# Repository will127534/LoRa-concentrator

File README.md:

# LoRa-concentrator

A Real opensource LoRa Gateway using SX1301/SX1308 and SX1255/SX1257
For RRI and RPI Zero

**Version 3**
---

Version 3 is designed for Raspberry Pi, same setup like Version 2, but I added LNA/PA and RF switch, and move to 4-layer board design
PA(RFPA0133) and RF switch(RFSW1012) is same as Microchip's LoRa gateway, but I changed LNA to SKY67150-396LF which have a much better Noise Figure(0.28dB).
Also note that I also used a wide bandwidth ceramic balun(800-1000Mhz) instead of discrete balun.

868Mhz and 915Mhz is mostly the same, just need to change four filter, both part number are in PCB files and BOM file. 

For power supply, 1.8V DC-DC step down has changed to TPS62061, but it is pin-to-pin replaceable with ETA3410. For 3.3V RF power, there is two option,
one is TPS7A470, which is a Ti's high-end LDO with 4 µVRMS noise, and 55dB PSRR, the other one is LP5912-3.3, which is cheaper but still gets 12 µVRMS noise and 75dB PSRR.

GPS module is still Max-7Q, which provide PPS to SX1301/8 and Raspberry Pi(GPIO05),
and provide NEMA through Raspberry Pi's UART port. There is a jumper for shuting down GPS module if you want to stack other board.

Lastly, it support PoE header on Raspberry Pi 3B+, so you can stack PoE hat on top of the board.(Just make it clear that the board doesn't have PoE on board, but just the pin header to support other PoE hat).

And is currently sold on Tindle!
https://www.tindie.com/products/will123321/sx1308-raspberry-pi-zero-lora-gateway-board/
https://www.tindie.com/products/will123321/sx1308-raspberry-pi-lora-gateway-board/

Update: 2021/08/22: The board has sold out!

**Version 2**
---
Version 2 is designed for Raspberry Pi and another board for Pi Zero

for Raspberry Pi, there is two SX125X, but for Pi Zero I strip down Radio_A for better layout.
Both of them have a Max-7Q GPS module, which provide PPS to SX1301 and Raspberry Pi(GPIO05),
and provide NEMA through Raspberry Pi's UART port. There's also a jumper for shuting down GPS module if you want to stack other board.

At the RF frontend, the main difference is that I didn't combine RX/TX using a RF switch,
and there is no on-board PA/LNA, but I did put a SAW filter. The reason not to is that I can use external LNA which is right under the antenna, there is a bias inductor right after RX port, which is connected to Raspberry Pi's 5V power rail.  

The current RPI version is designed for SX1257, but it is easy to migrate to SX1255, just put SX1255 on SX1257 and change RF passive components according to SX1255 datasheet.

I've tested both SX1255 & SX1257, and also two SX1301 connected to Raspberry Pi at the same time (there is a jumper for CE0/CE1).

last but not least, I've launch some High Altitude Balloon and using it as my multi-channel receiver. Which reach about 100Km by BW 125Khz CR 4/5 SF 7 @ 432Mhz with 16dBm power + MAX2640 LNA.

**Version 1**
---
note that I haven't get it working yet, stuck in PLL lock  
but SPI test seems to be OK.

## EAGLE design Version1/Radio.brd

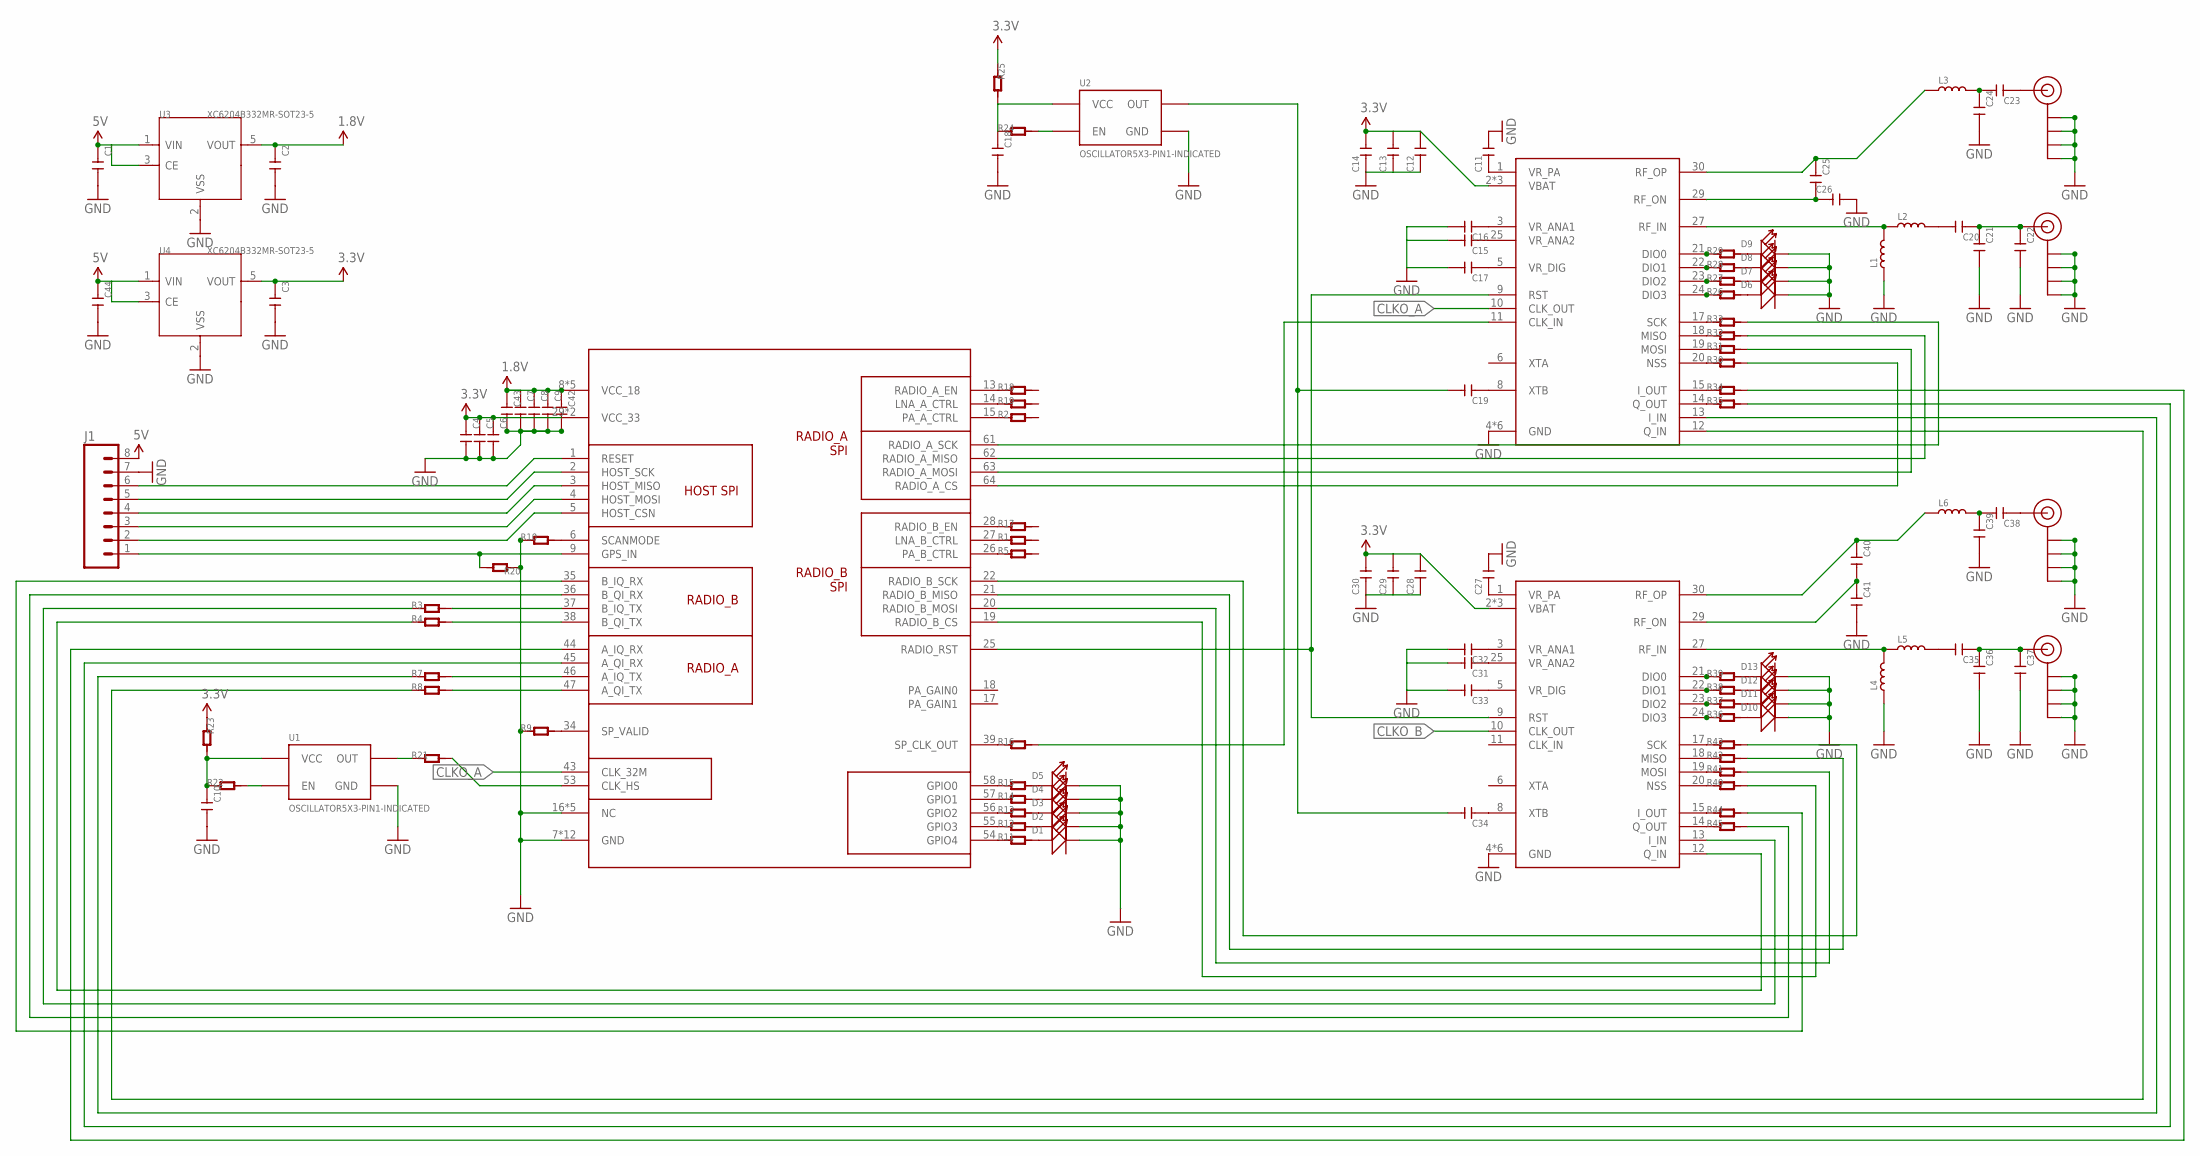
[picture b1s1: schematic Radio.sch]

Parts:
C1, C3: CAP-0603; C0603
C2, C4, C6, C7, C8, C9, C10, C11, C12, C13, C14, C15, C16, C17, C18, C19, C20, C21, C22, C23, C24, C25, C26, C27, C28, C29, C30, C31, C32, C33, C34, C35, C36, C37, C38, C39, C40, C41, C42, C43, C44: CAP-0402; C0402
C5: CAP-0805; C0805
D1, D2, D3, D4, D5, D6, D7, D8, D9, D10, D11, D12, D13: LED-0402
J1: M08LOCK; 1X08_LOCK
J$1, J$2, J$3, J$4: SMA_EDGE; SMA-EDGE
L1, L2, L3, L4, L5, L6: INDUCTOR/FERRITE-BEAD-0402; L0402
R1, R2, R3, R4, R5, R7, R8, R9, R10, R11, R12, R13, R14, R15, R16, R17, R18, R19, R20, R21, R22, R23, R24, R25, R26, R27, R28, R29, R30, R31, R32, R33, R34, R35, R36, R37, R38, R39, R40, R41, R42, R43, R44, R45: R-0402; R0402
U1, U2: OSCILLATOR5X3-PIN1-INDICATED; CRYSTAL-OSC-SMD-5X3
U3, U4: XC6204B332MR-SOT23-5; SOT-23-5
U$1: SX1301; QFN64G-0.5-9X9MM
U$2, U$3: SX1255; QFN32G-0.5-5X5MM

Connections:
1.8V: C2.1, C7.1, C8.1, C9.1, C42.1, C43.1, U3.5 (VOUT), U$1.8 (VCC_18), U$1.12 (VCC_18), U$1.23 (VCC_18), U$1.42 (VCC_18), U$1.60 (VCC_18)
3.3V: C3.1, C4.1, C5.1, C6.1, C12.2, C13.2, C14.2, C28.2, C29.2, C30.2, R23.1, R25.1, U4.5 (VOUT), U$1.29 (VCC_33), U$1.52 (VCC_33), U$2.2 (VBAT), U$2.16 (VBAT), U$2.32 (VBAT), U$3.2 (VBAT), U$3.16 (VBAT), U$3.32 (VBAT)
5V: C1.1, C44.1, J1.8, U3.1 (VIN), U3.3 (CE), U4.1 (VIN), U4.3 (CE)
CLKO_A: U$1.43 (CLK_32M), U$2.10 (CLK_OUT)
CLKO_B: U$3.10 (CLK_OUT)
CS: J1.2, U$1.5 (HOST_CSN)
GND: C1.2, C2.2, C3.2, C4.2, C5.2, C6.2, C7.2, C8.2, C9.2, C10.2, C11.2, C12.1, C13.1, C14.1, C15.2, C16.2, C17.2, C18.2, C21.2, C22.2, C24.2, C26.2, C27.2, C28.1, C29.1, C30.1, C31.2, C32.2, C33.2, C36.2, C37.2, C39.2, C41.2, C42.2, C43.2, C44.2, D1.-, D2.-, D3.-, D4.-, D5.-, D6.-, D7.-, D8.-, D9.-, D10.-, D11.-, D12.-, D13.-, J1.7, J$1.GND@0 (GND), J$1.GND@1 (GND), J$1.GND@2 (GND), J$1.GND@3 (GND), J$2.GND@0 (GND), J$2.GND@1 (GND), J$2.GND@2 (GND), J$2.GND@3 (GND), J$3.GND@0 (GND), J$3.GND@1 (GND), J$3.GND@2 (GND), J$3.GND@3 (GND), J$4.GND@0 (GND), J$4.GND@1 (GND), J$4.GND@2 (GND), J$4.GND@3 (GND), L1.1, L4.1, R9.1, R10.1, R20.1, U1.2 (GND), U2.2 (GND), U3.2 (VSS), U4.2 (VSS), U$1.7 (GND), U$1.10 (GND), U$1.11 (GND), U$1.16 (NC), U$1.24 (GND), U$1.30 (GND), U$1.31 (GND), U$1.32 (NC), U$1.33 (NC), U$1.40 (GND), U$1.41 (GND), U$1.48 (NC), U$1.49 (NC), U$1.50 (GND), U$1.51 (GND), U$1.59 (GND), U$1.65 (GND), U$2.4 (GND), U$2.7 (GND), U$2.26 (GND), U$2.28 (GND), U$2.31 (GND), U$2.33 (GND), U$3.4 (GND), U$3.7 (GND), U$3.26 (GND), U$3.28 (GND), U$3.31 (GND), U$3.33 (GND)
MISO: J1.4, U$1.3 (HOST_MISO)
MOSI: J1.3, U$1.4 (HOST_MOSI)
unnamed: R30.1, U$2.20 (NSS)
unnamed: R45.2, U$1.36 (B_QI_RX)
unnamed: R3.2, U$1.37 (B_IQ_TX)
unnamed: R4.2, U$1.38 (B_QI_TX)
unnamed: R34.2, U$1.44 (A_IQ_RX)
unnamed: R7.2, U$1.46 (A_IQ_TX)
unnamed: R8.2, U$1.47 (A_QI_TX)
unnamed: R35.2, U$1.45 (A_QI_RX)
unnamed: R9.2, U$1.34 (SP_VALID)
unnamed: R10.2, U$1.6 (SCANMODE)
unnamed: R1.1, U$1.27 (LNA_B_CTRL)
unnamed: R11.1, U$1.54 (GPIO4)
unnamed: R12.1, U$1.55 (GPIO3)
unnamed: R13.1, U$1.56 (GPIO2)
unnamed: R14.1, U$1.57 (GPIO1)
unnamed: R15.1, U$1.58 (GPIO0)
unnamed: D1.+, R11.2
unnamed: D2.+, R12.2
unnamed: D4.+, R14.2
unnamed: D5.+, R15.2
unnamed: D3.+, R13.2
unnamed: R16.1, U$1.39 (SP_CLK_OUT)
unnamed: R17.1, U$1.28 (RADIO_B_EN)
unnamed: R18.1, U$1.13 (RADIO_A_EN)
unnamed: R2.1, U$1.15 (PA_A_CTRL)
unnamed: R19.1, U$1.14 (LNA_A_CTRL)
unnamed: R5.1, U$1.26 (PA_B_CTRL)
unnamed: C19.1, U$2.8 (XTB)
unnamed: R21.2, U$1.53 (CLK_HS)
unnamed: R21.1, U1.3 (OUT)
unnamed: R22.2, U1.1 (EN)
unnamed: C10.1, R22.1, R23.2, U1.4 (VCC)
unnamed: R24.2, U2.1 (EN)
unnamed: C11.1, U$2.1 (VR_PA)
unnamed: C18.1, R24.1, R25.2, U2.4 (VCC)
unnamed: C19.2, C34.2, U2.3 (OUT)
unnamed: C15.1, U$2.25 (VR_ANA2)
unnamed: C16.1, U$2.3 (VR_ANA1)
unnamed: C17.1, U$2.5 (VR_DIG)
unnamed: R26.1, U$2.24 (DIO3)
unnamed: R27.1, U$2.23 (DIO2)
unnamed: R28.1, U$2.22 (DIO1)
unnamed: R29.1, U$2.21 (DIO0)
unnamed: D6.+, R26.2
unnamed: D8.+, R28.2
unnamed: D9.+, R29.2
unnamed: D7.+, R27.2
unnamed: L1.2, L2.1, U$2.27 (RF_IN)
unnamed: C20.2, L2.2
unnamed: C20.1, C21.1, C22.1, J$1.SIG (SIGNAL)
unnamed: C23.2, C24.1, L3.2
unnamed: C25.1, L3.1, U$2.30 (RF_OP)
unnamed: C25.2, C26.1, U$2.29 (RF_ON)
unnamed: C23.1, J$2.SIG (SIGNAL)
unnamed: R34.1, U$2.15 (I_OUT)
unnamed: R35.1, U$2.14 (Q_OUT)
unnamed: C27.1, U$3.1 (VR_PA)
unnamed: C31.1, U$3.25 (VR_ANA2)
unnamed: C32.1, U$3.3 (VR_ANA1)
unnamed: C33.1, U$3.5 (VR_DIG)
unnamed: C34.1, U$3.8 (XTB)
unnamed: R36.1, U$3.24 (DIO3)
unnamed: R37.1, U$3.23 (DIO2)
unnamed: R38.1, U$3.22 (DIO1)
unnamed: R39.1, U$3.21 (DIO0)
unnamed: D10.+, R36.2
unnamed: D12.+, R38.2
unnamed: D13.+, R39.2
unnamed: D11.+, R37.2
unnamed: L4.2, L5.1, U$3.27 (RF_IN)
unnamed: C35.2, L5.2
unnamed: C35.1, C36.1, C37.1, J$3.SIG (SIGNAL)
unnamed: C38.2, C39.1, L6.2
unnamed: C40.1, L6.1, U$3.30 (RF_OP)
unnamed: C40.2, C41.1, U$3.29 (RF_ON)
unnamed: C38.1, J$4.SIG (SIGNAL)
unnamed: R44.1, U$3.15 (I_OUT)
unnamed: R45.1, U$3.14 (Q_OUT)
unnamed: R33.2, U$1.61 (RADIO_A_SCK)
unnamed: R32.2, U$1.62 (RADIO_A_MISO)
unnamed: R31.2, U$1.63 (RADIO_A_MOSI)
unnamed: R30.2, U$1.64 (RADIO_A_CS)
unnamed: R43.2, U$1.22 (RADIO_B_SCK)
unnamed: R42.2, U$1.21 (RADIO_B_MISO)
unnamed: R41.2, U$1.20 (RADIO_B_MOSI)
unnamed: R40.2, U$1.19 (RADIO_B_CS)
unnamed: U$1.25 (RADIO_RST), U$2.9 (RST), U$3.9 (RST)
unnamed: R16.2, U$2.11 (CLK_IN)
unnamed: R44.2, U$1.35 (B_IQ_RX)
unnamed: R7.1, U$2.13 (I_IN)
unnamed: R3.1, U$3.13 (I_IN)
unnamed: R4.1, U$3.12 (Q_IN)
unnamed: R8.1, U$2.12 (Q_IN)
unnamed: R31.1, U$2.19 (MOSI)
unnamed: R32.1, U$2.18 (MISO)
unnamed: R33.1, U$2.17 (SCK)
unnamed: R40.1, U$3.20 (NSS)
unnamed: R41.1, U$3.19 (MOSI)
unnamed: R42.1, U$3.18 (MISO)
unnamed: R43.1, U$3.17 (SCK)
PPS: J1.1, R20.2, U$1.9 (GPS_IN)
RST: J1.6, U$1.1 (RESET)
SCK: J1.5, U$1.2 (HOST_SCK)

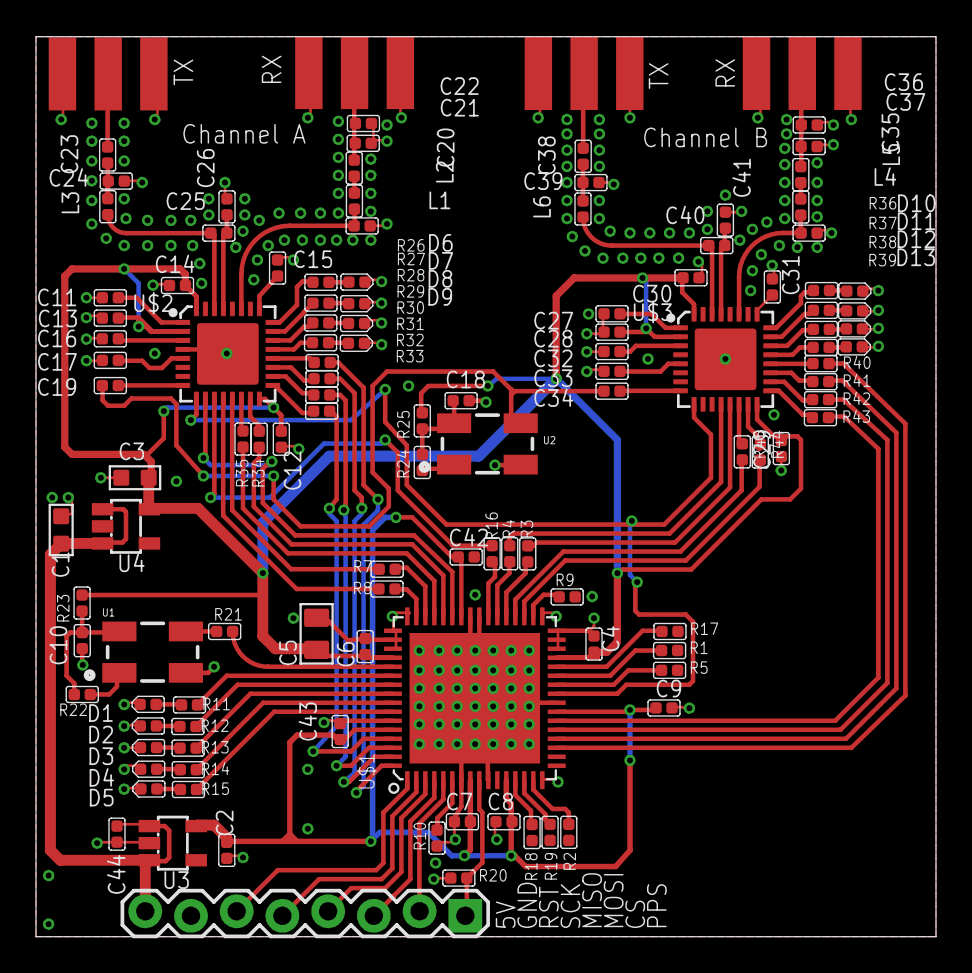
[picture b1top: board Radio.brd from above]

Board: 2 copper layers, 50.0 x 50.0 mm, 119 parts (0 on the bottom side), 111 nets.

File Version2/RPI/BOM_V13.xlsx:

Qty | Value | Device | Package | Parts
1 | ETA3410D2I | PMIC | WSON | U1
6 | 0R | Resistor | 0402 | R9, R10, R21, R22, R23, R25
6 | 100R | Resistor | 0402 | R3, R4, R7, R8, R16, R18
13 | 100nF | Capacitor | 0402 | C4, C6, C8, C9, C15, C16, C17, C18, C31, C32, C33, C42, C43
8 | 10K | Resistor | 0402 | R6, R20, R30, R32, R33, R40, R42,R43
1 | 10R | Resistor | 0402 | R2
3 | 10nF | Capacitor | 0402 | C10, C11, C27
1 | LQG15HN10NH02D | Inductor | 0402 | L3
1 | 10pF | Capacitor | 0402 | C23
3 | 10uF | Capacitor | 0603 | C1, C3, C35
1 | 120K | Resistor | 0402 | R1
3 | 1K | Resistor | 0402 | R17, R31, R41
2 | 1nF | Capacitor | 0402 | C19, C34
7 | 1uF | Capacitor | 0402 | C7, C12, C13, C14, C28, C29, C30
1 | 1uH | Power Inductor | 1616BZ | L4
1 | 22pF | Capacitor | 0402 | C36
1 | GRM21BR60J226ME39L | Capacitor | 0603 | C5
2 | 3.3pF | Capacitor | 0402 | C24, C25
4 | 330R | Resistor | 0402 | R34, R35, R44, R45
1 | 33pF | Capacitor | 0402 | C26
5 | 470R | Resistor | 0402 | R11, R12, R13, R14, R15
2 | 56pF | Capacitor | 0402 | C2,C20
1 | 60.4K | Resistor | 0402 | R5
1 | B39921B3728U410 | SAW | EPCOS_SAW_FILTER | U$4
1 | ESD7371XV2T1G | ESD Diode | SOD523 | D6
1 | GRM1555C1E470JZ01 | Capacitor | 0402 | C21
4 | Green | LED | 0603 | D0, D1, D2, D3
1 | LQG15HS27NJ02 | Inductor | 0402 | L6
1 | LQG15HS33NJ02D | Inductor | 0402 | L1
1 | LQG15HS3N9C02D | Inductor | 0402 | L2
1 | MAX-7Q | GPS Module | GPS | GPS
1 | 32Mhz | Oscillator | 3.2X2.5 | OSC2
1 | DSC1025BC2-133.0000 | Oscillator | 5X3 | OSC1
1 | PMEG1030EJ,115 | Diode | SOD323 | D5
1 | Red | LED | 0603 | D4
2 | SX1257 | SX1255 | QFN32G-0.5-5X5MM | U$2, U$3
1 | SX1308 | SX1301 | QFN64G-0.5-9X9MM | U$1
3 | uFL | UFLCONNECTOR |  | X4, X2, X3
1 | 2x20 2.54mm Pin | Pin connector
1 | 5.6pF | Capacitor | 0402 | C22

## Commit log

2016-08-29 init
2016-08-29 upload Picture
2017-08-12 Adding Version 2
    Design for Raspberry Pi Zero
2017-08-14 Update licence
    Just notice that original licence is for software....
    So I copied MIT licence template from OSHW.
2017-09-01 add version 2 picture
2017-09-01 clean up
2017-12-01 release RPI Version
2018-04-04 Add BOM file
2018-05-26 Adding RPI V1.5
2018-07-31 Added RPi IO mapping table to version 3 directory README.md
2018-10-24 Adding the smallest full setup Gateway for RPI Zero!
2019-03-02 Fix the version problem of V3 RPI, the boards sellign on Tindle are updated
2019-03-25 issue #30
2019-04-05 Adding Gerber files

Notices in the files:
parts and their libraries:
SparkFun-Aesthetics: Licensing: Creative Commons ShareAlike 4.0 International - https://creativecommons.org/licenses/by-sa/4.0
